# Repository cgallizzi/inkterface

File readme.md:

# Inkterface: Now Playing Edition

An e-ink faceplate for your Steam Machine that shows the box art, playtime,
and achievement progress of whatever you're playing — plus all the original
system telemetry readouts.

> This is a community fork of
> [Valve's Inkterface](https://gitlab.steamos.cloud/SteamHardware/SteamMachine/inkterface),
> created by NaKyle Wright at Valve and released under the MIT license.
> All of the hardware design, assembly docs, and the original firmware and
> companion app are their work — this fork adds the artwork/"now playing"
> features and easier install tooling on top. Thank you Valve for open
> sourcing it!

## What this fork adds

* **Now Playing artwork mode**: when you launch a game, the panel switches to
  that game's box art with your total playtime and achievement progress
  rendered next to it (dithered for the e-ink look). When you quit, it goes
  back to the regular telemetry layout. Toggle it with the `Box Art` button
  in the configure screen.
* **Game collectors**: `Game Time` and `Achievements` readouts you can put in
  any panel field, alongside the stock CPU/GPU/fan stats.
* **Browser firmware flasher**: flash your Feather from Chrome/Edge at the
  project's GitHub Pages site — no toolchain install needed.
* **One-line app install**: paste a single command on your Steam Machine and
  you're done — no building, no USB sticks.

Achievement data comes from the Steam Community profile endpoint and requires
no API key, but your profile's game details need to be public for it to show.

## Quick Install (this fork)

**Firmware** — plug the Feather into any PC over USB and open the
[web flasher](https://cgallizzi.github.io/inkterface/) in Chrome or Edge, then
click Install for your board.

**App** — on the Steam Machine, open a terminal in desktop mode and run:

```sh
curl -fsSL https://raw.githubusercontent.com/cgallizzi/inkterface/main/scripts/install.sh | sh
```

That downloads the latest release to `~/Applications`, launches it, and from
there you pick your panel and click Install (bottom right) to set up the
background service. Prebuilt AppImages are also on the
[releases page](https://github.com/cgallizzi/inkterface/releases) if you'd rather
grab one manually.

Everything below is the original upstream documentation for building the
hardware and working from source.

## Required Hardware

* 1 x Adafruit ESP32-S3 Feather w/ 2MB PSRAM
    * [Link to V1 Board, as shown in the assembly video and document!](https://www.adafruit.com/product/5477)
    * [Link to V2 Board, accidentally the only link previously!](https://www.adafruit.com/product/5400)
    * Both the V1 and V2 modules work, but they have different pinouts, make sure
      to check if you see the "V2" silkscreen on your board and choose the correct
      pinout sheet and environment when building the firmware!
* 1 x [Adafruit eInk Breakout Friend](https://www.adafruit.com/product/4224)
* 1 x [Adafruit 5.83" Monochrome eInk Panel](https://www.adafruit.com/product/6397)
* 1 x [LP803860 Battery](https://www.adafruit.com/product/2011)
* 13 x M2.5 x 5mm Pan Head Machine Screws
    * [McMaster](https://www.mcmaster.com/92000A103/)
    * [Amazon](https://www.amazon.com/dp/B0GC58C2V5)
* 4 x [1/4" x 1/4" x 3/16" Stepped Magnet SB443-OUT](https://www.kjmagnetics.com/sb443-out-neodymium-stepped-block-magnet)

## Assembly

Check out the assembly tutorial video in
[the upstream repo](https://gitlab.steamos.cloud/SteamHardware/SteamMachine/inkterface/-/blob/main/docs/Inkterface%20Assembly.mp4)
(kept out of this fork because it exceeds GitHub's file size limit),
or if you'd prefer there is a PDF version too `./docs/Inkterface Assembly.pdf`.

**_Warning: The screws will thread themselves into the plastic, but be VERY gentle
as it is easy to strip the plastic away and you may need to re-print parts!_**

1. Print parts from `./cad` folder.
    * Individual parts are included as separate STEP files, but a combined file
      with all parts that is ready for printing on a Stratasys F370 build plate
      is also provided as `Inkterface - Print Plate.step`.
2. Attach the ESP32 Feather and eInk Breakout to the board plate layer using 4x screws.
    * Having them held in place helps with soldering the connections and sizing your wires.
3. Solder wires between the pins of the two boards.
    * MOSI/MISO/SCK/GND all connect directly as expected.
    * 3V3 from the feather connects to VIN on the breakout.
        * The 3V3 pin on the breakout is a 3V3 output.
    * For the **_V1_** feather connect these pins, like Feather -> Breakout:
        * PIN 6 -> ENA
        * PIN 9 -> BUSY
        * PIN 10 -> RST
        * PIN 11 -> SRCS
        * PIN 12 -> D/C
        * PIN 13 -> ECS
    * For the **_V2_** feather connect these pins, like Feather -> Breakout:
        * PIN 32 -> ENA
        * PIN 15 -> BUSY
        * PIN 33 -> RST
        * PIN 27 -> SRCS
        * PIN 12 -> D/C
        * PIN 13 -> ECS
    * **_NOTE:_** On both feather versions we connect to pins in the same physical
        positions, but they are different logical pins in the firmware.
4. Place the e-ink panel into the matching recess in the faceplate part.
5. Fit the two midplates in.
6. Place the 4 magnets into the recesses in each corner of of the midplates.
    * Magnetic field orientation doesn't matter, they connect to metal slugs
      in the Steam Machine chassis.
7. Place the board plate over the midplates, aligning the magnets and screw holes.
8. Fasten the boardplate with 8x screws in the screw holes along the edges.
9. Connect the e-ink panel to the breakout board.
    * Be careful when handling the flex that comes out of the panel, it is fragile
      and should not be bent or folded.
10. Place the battery in the recess, tucking its wire under the board plate and
    up into the clearance hole beside the feather.
11. Insert and fasten down the battery retainer/cover.
12. Plug the battery connecor into the feather.

Once you've assembled the unit it should be fairly solid and easily magnet to the
front of a Steam Machine!

You will need to build/flash the firmware onto the feather using the steps below.

## Usage

[Eventually we'll have an app up on Steam](https://store.steampowered.com/app/1222770)
but until then you can build an AppImage using the instructions further down in
this readme.

Once you have it built, take a look at `./docs/Inkterface Setup.pdf`, but the
basics are:
1. Enable bluetooth.
2. In desktop mode register as an app in Steam.
    * Or you can just run it directly.
3. Wait for it to discover your panel.
    * If it doesn't appear try clicking the reset button on the back and checking
      that bluetooth is enabled.
4. Select your panel, the name shown should match what's displayed on the inkterface.
    * They all start with an `INKTF-` prefix and then use a unique portion of the
      panels BLE MAC address.
5. On the configure screen, install the service using the button at the bottom
   right.
    * This will set itself up as a user service, so don't move the AppImage or
      that will break, no biggie though, you'll just need to re-run it.
    * Once the service is installed it might take 10-20 seconds for it to connect
      to the inkterface, that's fine, it just needs to go through discovery.
6. Finally you can click any of the readouts to adjust what they display.
    * We have several stats built in, but if you check out `include/panel-state.hpp`
      you can add any function that can return a `QString` or `double` and then
      `registerCollector()` to have it show up in the list.
      * There are some examples of stateful and idempotent collectors in `SysStats`,
        they get registered in the `PanelState` constructor.
7. Exit the configuration app.
    * The service is lightweight and runs in the background, you only need to
      run the config software to select a panel or to change what it displays.

## Building Interface

If you have Qt installed you should be able to open the cmake project in Qt Creator
and use that.

For better distributable builds you can setup a container for wider platform
support using the included `Containerfile`.

1. `podman build -t qt69-builder -f ./Containerfile`
2. `distrobox create --image qt69-builder --name qt69`
3. `distrobox enter qt69`
4. `./scripts/build.sh deploy`

That should produce an AppImage for you in the `./dist-linux-x86_64` folder.

This container uses an older version of Ubuntu and Qt 6.9 which should let us
build AppImages that will work on a wide range of modern systems.

## Building Firmware

For a mix of convenience and approachability this project uses
[PlatformIO](https://platformio.org), and in particular here you'll use the
[pio run](https://docs.platformio.org/en/latest/core/userguide/cmd_run.html)
command. Reading up on them can be useful, especial options like `--upload-port`
which could help if you have multiple serial ports.

If you're using the container from above you can just do:

1. `distrobox enter qt69`
2. `cd ./firmware`
3. If you have a **_V1_** feather: `pio run -e featherv1 -t upload`
4. If you have a **_V2_** feather: `pio run -e featherv2 -t upload`

And it should build and flash the firmware, if you want to get setup manually:

1. Install [PlatformIO](https://platformio.org) for your system.
2. `cd ./firmware`
3. If you have a **_V1_** feather: `pio run -e featherv1 -t upload`
4. If you have a **_V2_** feather: `pio run -e featherv2 -t upload`

Of course in both cases you need to have the ESP32 Feather attached via USB and
permission to interact with serial devices on your system.

**_NOTE:_** You can add build definitions and support for other boards by modifying
the `platformio.ini`, check it out to see the V1 and V2 feather environments.

## Design Docs

Planning out the UI and panel design is done in a Lunacy document you can find
in the `./design` folder.

Lunacy is an open source alternative to tools like Figma that can work entirely
offline.

## License

This project is licensed under the MIT License, see LICENSE.

This project depends on third-party software that is distributed under its own
licenses. Those licenses remain applicable to the respective components and
are not modified by this project's license.

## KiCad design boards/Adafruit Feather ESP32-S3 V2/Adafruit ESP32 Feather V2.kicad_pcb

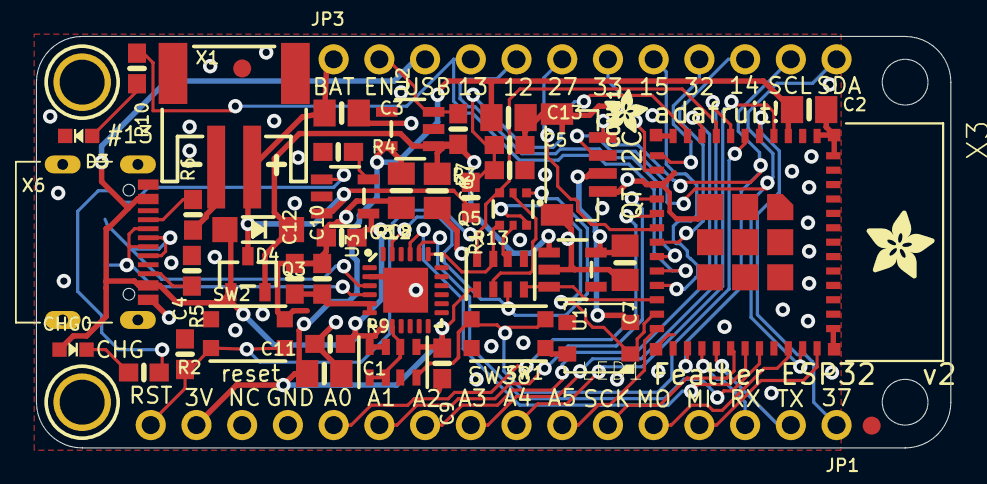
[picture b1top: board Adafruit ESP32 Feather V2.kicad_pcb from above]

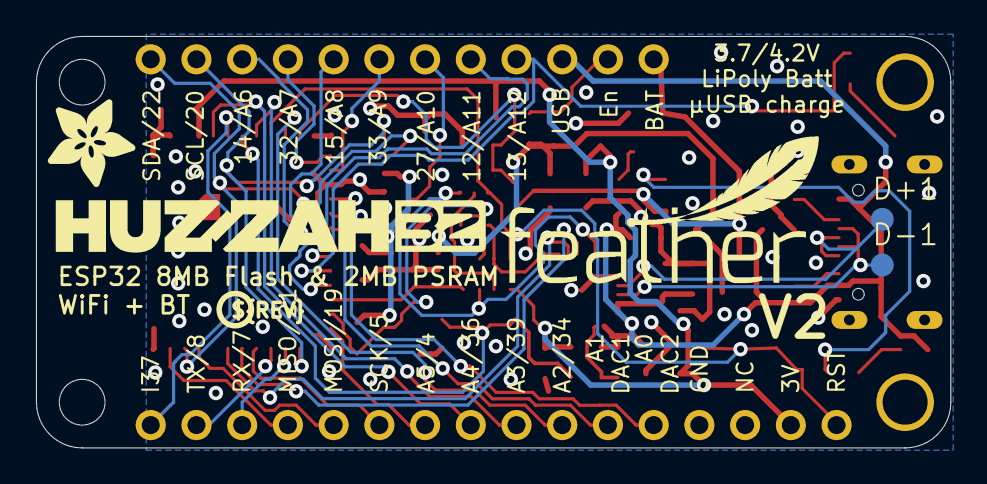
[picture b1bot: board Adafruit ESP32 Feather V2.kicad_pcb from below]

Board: 2 copper layers, 50.8 x 22.9 mm, 56 parts (6 on the bottom side), 49 nets.

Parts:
C1, C2, C13: 10uF; 0805-NO
C3, C6, C7, C8: 10µF; 0805-NO
C4, C5, C9, C10: 1uF; 0603-NO
C11, C12: 0.1uF; 0603-NO
CHG0: ORANGE; CHIPLED_0603_NOOUTLINE
CONN1: STEMMA_I2C_QTRA; JST_SH4_RA
D3: RED; CHIPLED_0603_NOOUTLINE
D4: MBR540; SOD-123
D+1: TPB1,27; B1,27_385
D-1: TPB1,27; B1,27_385
IC3: CP2102N-24; QFN24_4MM_SMSC
JP1: 1X16_ROUND
JP3: 1X12_ROUND
LED1: WS2812B3535; LED3535
Q3: DMG3415U; SOT23-R
Q5: DUAL NPN; SOT363
R1, R3: 200K; 0603-NO
R2, R4, R5, R6, R10: 5.1K; 0603-NO
R7, R12: 100K; 0603-NO
R9: 47K; RESPACK_4X0603
R13: 10K; RESPACK_4X0603
SW1, SW2: KMR2; BTN_KMR2_4.6X2.8
U1, U2: AP2112-3.3; SOT23-5
U3: MCP73831T-2ACI/OT; SOT23-5
U$7: ADAFRUIT_5MM
U$9: FEATHERLOGO_MED
U$13: PCBFEAT-REV-040
U$14: ADAFRUIT_2.5MM
U$15: ADAFRUIT_3.5MM
U$31, U$32: MOUNTINGHOLE2.5; MOUNTINGHOLE_2.5_PLATED
U$34, U$35: FIDUCIAL_1MM
U$43: HUZZAH32
UNK_HOLE_0: dummyfp0
UNK_HOLE_1: dummyfp1
X1: JSTPH; JSTPH2_BATT
X3: ESP32-PICO-MINI-02MINI; ESP32-PICO-MINI
X6: USB Type C; USB_C_CUSB31-CFM2AX-01-X

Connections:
3.3V: C1.1, C2.1, C8.1, C9.1, C13.1, JP1.15, R9.5, R13.1, U2.5, X3.3
3.45V: C10.1, C12.1, IC3.5, IC3.6
A0_DAC2: JP1.12, X3.16
A1_DAC1: JP1.11, X3.15
A2_I34: JP1.10, X3.9
A3_I39: JP1.9, X3.7
A4_I36: JP1.8, X3.4
A5_IO4: JP1.7, X3.24
A13_I35: C5.1, R1.1, R3.2, X3.10
CC1: R6.2, X6.A5
CC2: R5.2, X6.B5
D+: D+1.TP, IC3.3, X6.A6, X6.B6
D-: D-1.TP, IC3.4, X6.A7, X6.B7
DTR: IC3.23, Q5.1, R13.3
EN: JP3.2, R7.1, U2.3
GND: C1.2, C2.2, C3.2, C4.2, C5.2, C6.2, C7.2, C8.2, C9.2, C10.2, C11.2, C12.2, C13.2, CONN1.1, CONN1.MT1, CONN1.MT2, D3.C, IC3.2, IC3.THERM, JP1.13, LED1.4, R3.1, R4.1, R5.1, R6.1, R9.3, R12.1, R13.5, SW1.A, SW1.A', SW2.A, SW2.A', U1.2, U2.2, U3.2, X1.1, X1.NC1, X1.NC2, X3.1, X3.2, X3.11, X3.14, X3.36, X3.37, X3.38, X3.39, X3.40, X3.41, X3.42, X3.43, X3.44, X3.45, X3.46, X3.47, X3.48, X3.49, X3.50, X3.51, X3.52, X3.53, X3.54, X3.55, X3.56, X3.57, X3.58, X3.59, X3.60, X3.61, X6.A1B12, X6.B1A12
GPIO0: LED1.1, Q5.6, X3.23
I37: JP1.1, X3.5
IO12_A11: JP3.5, X3.19
IO13_A12: JP3.4, R10.1, X3.20
IO14_A6: JP3.10, X3.18
IO15_A8: JP3.8, X3.21
IO27_A10: JP3.6, X3.17
IO32_A7: JP3.9, X3.12
IO33_A9: JP3.7, X3.13
MISO: JP1.4, X3.35
MOSI: JP1.5, X3.33
unnamed: CHG0.C, R2.1
unnamed: R2.2, U3.1
unnamed: R4.2, U3.5
unnamed: D3.A, R10.2
unnamed: R9.4, SW1.B, SW1.B', X3.6
unnamed: Q5.5, R13.6
unnamed: Q5.2, R13.2
NEOI2C_PWR: R13.4, U1.3, X3.22
RTS: IC3.19, Q5.4, R13.7
RX/IO7: JP1.3, X3.27
RXD0: IC3.21, X3.30
SCK: JP1.6, X3.29
SCL: CONN1.4, JP3.11, X3.26
SDA: CONN1.3, JP3.12, X3.34
TX/IO8: JP1.2, X3.28
TXD0: IC3.20, X3.31
VBAT: C3.1, JP3.1, Q3.3, R1.2, U3.3, X1.2
VBUS: C11.1, CHG0.A, D4.A, IC3.7, JP3.3, Q3.1, R9.7, R9.8, R12.2, U3.4, X6.A4B9, X6.B4A9
VBUS_DET: IC3.8, R9.1, R9.2, R9.6
VHI: C6.1, D4.C, Q3.2, R7.2, U1.1, U2.1
V_NEOI2C: C7.1, CONN1.2, LED1.2, U1.5
~RESET: C4.1, JP1.16, Q5.3, R13.8, SW2.B, SW2.B', X3.8

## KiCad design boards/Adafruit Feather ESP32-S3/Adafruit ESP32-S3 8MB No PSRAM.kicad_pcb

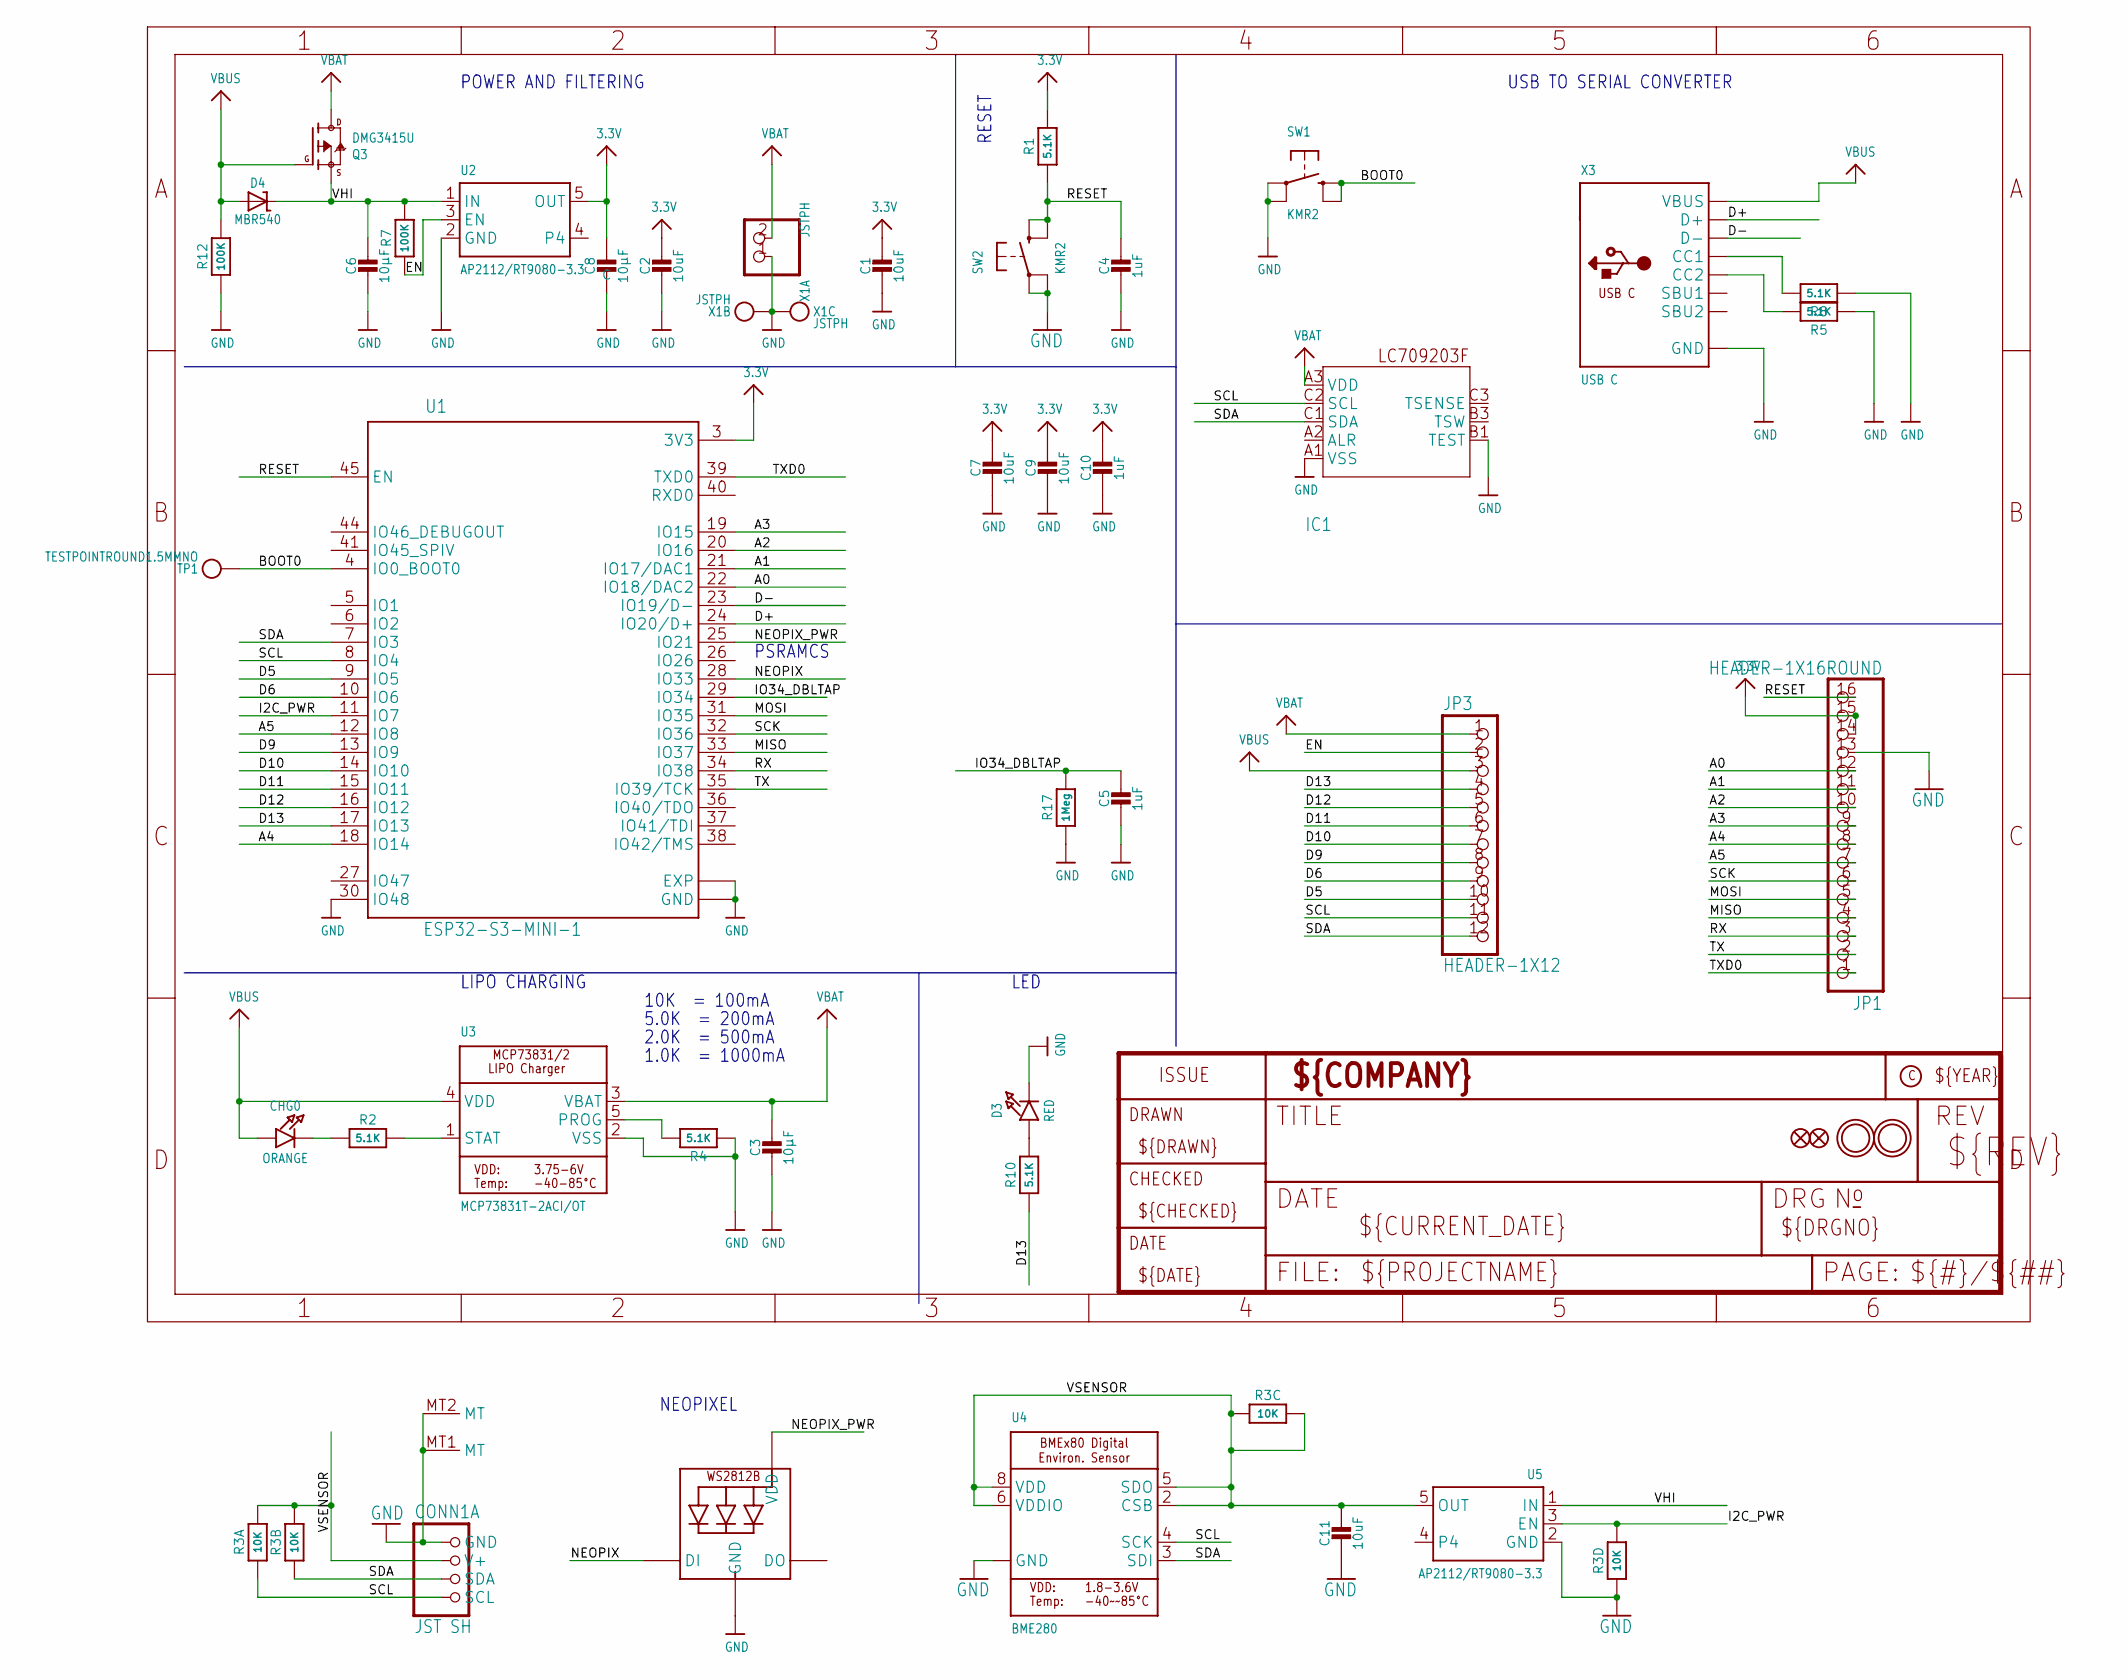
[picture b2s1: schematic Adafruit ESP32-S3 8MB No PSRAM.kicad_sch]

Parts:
C1, C2, C7, C9: 10uF; 0805-NO
C3, C6, C8: 10µF; 0805-NO
C4, C5, C10: 1uF; 0603-NO
C11: 10uF; _0805MP
CHG0: ORANGE; CHIPLED_0603_NOOUTLINE
CONN1: JST SH; JST_SH4_RA
D3: RED; CHIPLED_0603_NOOUTLINE
D4: MBR540; SOD-123
IC1: LC709203F/MH; WLCSP9
JP1: HEADER-1X16ROUND; 1X16_ROUND
JP3: HEADER-1X12; 1X12_ROUND
LED1: WS2812B_SK6805_1515; SK6805_1515
Q3: DMG3415U; SOT23-R
R1, R2, R4, R5, R8, R10: 5.1K; 0603-NO
R3: 10K; RESPACK_4X0603
R7, R12: 100K; 0603-NO
R17: 1Meg; 0603-NO
SW1, SW2: KMR2; BTN_KMR2_4.6X2.8
TP1: TESTPOINTROUND1.5MMNO; TESTPOINT_ROUND_1.5MM_NO
U1: ESP32-S3-MINI-1; QFN60_ESP32-S2-MINI-1_EXP
U2, U5: AP2112/RT9080-3.3; SOT23-5
U3: MCP73831T-2ACI/OT; SOT23-5
U4: BME280
U$31, U$32: MOUNTINGHOLE2.5; MOUNTINGHOLE_2.5_PLATED
U$34, U$35: FIDUCIAL_1MM
X1: JSTPH; JSTPH2_BATT
X3: USB C; USB_C_CUSB31-CFM2AX-01-X

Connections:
3.3V: C1.1, C2.1, C7.1, C8.1, C9.1, C10.1, JP1.14, JP1.15, R1.2, U1.3 (3V3), U2.5 (OUT)
A0: JP1.12, U1.22 (IO18/DAC2)
A1: JP1.11, U1.21 (IO17/DAC1)
A2: JP1.10, U1.20 (IO16)
A3: JP1.9, U1.19 (IO15)
A4: JP1.8, U1.18 (IO14)
A5: JP1.7, U1.12 (IO8)
BOOT0: SW1.B (S), SW1.B' (S1), TP1.P$1, U1.4 (IO0_BOOT0)
D5: JP3.10, U1.9 (IO5)
D6: JP3.9, U1.10 (IO6)
D9: JP3.8, U1.13 (IO9)
D10: JP3.7, U1.14 (IO10)
D11: JP3.6, U1.15 (IO11)
D12: JP3.5, U1.16 (IO12)
D13: JP3.4, R10.1, U1.17 (IO13)
D+: U1.24 (IO20/D+), X3.A6 (D+), X3.B6 (D+)
D-: U1.23 (IO19/D-), X3.A7 (D-), X3.B7 (D-)
EN: JP3.2, R7.1, U2.3 (EN)
GND: C1.2, C2.2, C3.2, C4.2, C5.2, C6.2, C7.2, C8.2, C9.2, C10.2, C11.2, CONN1.1 (GND), CONN1.MT1 (MT), CONN1.MT2 (MT), D3.C, IC1.A1 (VSS), IC1.B1 (TEST), JP1.13, LED1.4 (GND), R3.4 (1), R4.1, R5.1, R8.1, R12.1, R17.1, SW1.A, SW1.A' (P1), SW2.A, SW2.A' (P1), U1.1 (GND), U1.2 (GND), U1.30 (IO48), U1.42 (GND), U1.43 (GND), U1.46 (GND), U1.47 (GND), U1.48 (GND), U1.49 (GND), U1.50 (GND), U1.51 (GND), U1.52 (GND), U1.53 (GND), U1.54 (GND), U1.55 (GND), U1.56 (GND), U1.57 (GND), U1.58 (GND), U1.59 (GND), U1.60 (GND), U1.61 (EXP), U1.62 (GND), U1.63 (GND), U1.64 (GND), U1.65 (GND), U1.66 (EXP), U1.67 (EXP), U1.68 (EXP), U1.69 (EXP), U1.70 (EXP), U1.71 (EXP), U1.72 (EXP), U1.73 (EXP), U2.2 (GND), U3.2 (VSS), U4.1 (GND), U4.7 (GND), U5.2 (GND), X1.1, X1.NC1, X1.NC2, X3.A1B12 (GND), X3.B1A12 (GND)
I2C_PWR: R3.5 (2), U1.11 (IO7), U5.3 (EN)
IO34_DBLTAP: C5.1, R17.2, U1.29 (IO34)
MISO: JP1.4, U1.33 (IO37)
MOSI: JP1.5, U1.31 (IO35)
unnamed: CHG0.C, R2.1
unnamed: R2.2, U3.1 (STAT)
unnamed: R4.2, U3.5 (PROG)
unnamed: D3.A, R10.2
unnamed: R8.2, X3.A5 (CC1)
unnamed: R5.2, X3.B5 (CC2)
NEOPIX: LED1.1 (DI), U1.28 (IO33)
NEOPIX_PWR: LED1.2 (VDD), U1.25 (IO21)
RESET: C4.1, JP1.16, R1.1, SW2.B (S), SW2.B' (S1), U1.45 (EN)
RX: JP1.3, U1.34 (IO38)
SCK: JP1.6, U1.32 (IO36)
SCL: CONN1.4 (SCL), IC1.C2 (SCL), JP3.11, R3.1, U1.8 (IO4), U4.4 (SCK)
SDA: CONN1.3 (SDA), IC1.C1 (SDA), JP3.12, R3.2 (1), U1.7 (IO3), U4.3 (SDI)
TX: JP1.2, U1.35 (IO39/TCK)
TXD0: JP1.1, U1.39 (TXD0)
VBAT: C3.1, IC1.A3 (VDD), JP3.1, Q3.3 (D), U3.3 (VBAT), X1.2
VBUS: CHG0.A, D4.A, JP3.3, Q3.1 (G), R12.2, U3.4 (VDD), X3.A4B9 (VBUS), X3.B4A9 (VBUS)
VHI: C6.1, D4.C, Q3.2 (S), R7.2, U2.1 (IN), U5.1 (IN)
VSENSOR: C11.1, CONN1.2 (V+), R3.3 (1), R3.6 (2), R3.7 (2), R3.8 (2), U4.2 (CSB), U4.5 (SDO), U4.6 (VDDIO), U4.8 (VDD), U5.5 (OUT)

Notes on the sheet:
NEOPIXEL
5.0K = 200mA
RESET
1.0K = 1000mA
POWER AND FILTERING
LIPO CHARGING
USB TO SERIAL CONVERTER
2.0K = 500mA
PSRAMCS
10K = 100mA
LED

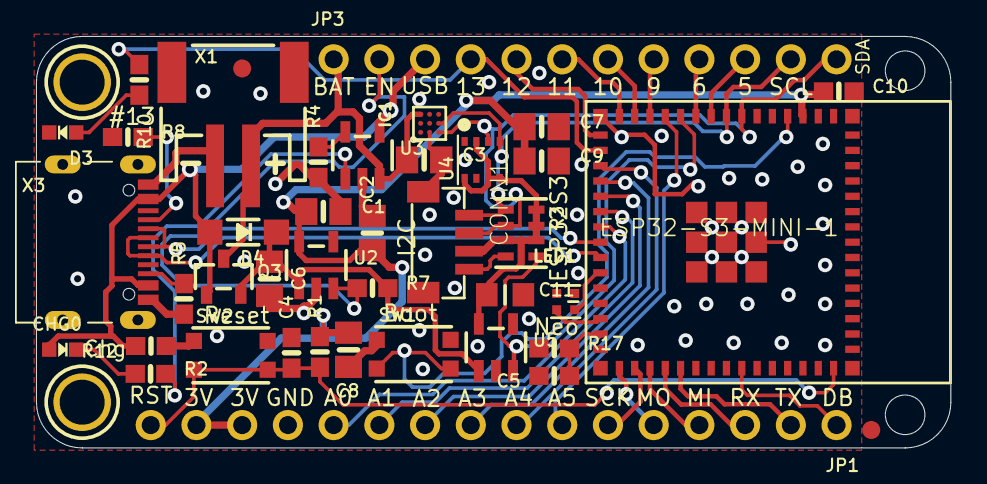
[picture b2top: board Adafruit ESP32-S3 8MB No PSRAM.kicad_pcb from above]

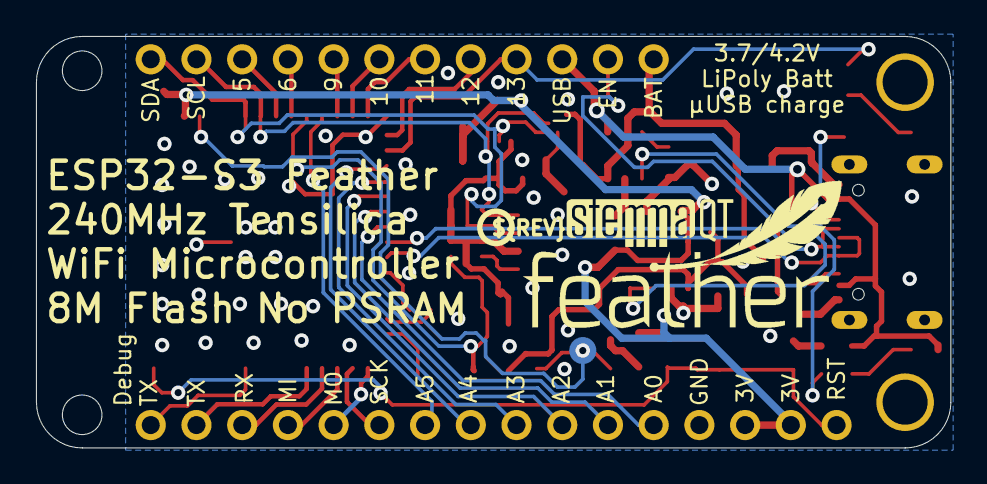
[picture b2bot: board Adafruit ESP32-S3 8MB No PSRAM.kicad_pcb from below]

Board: 2 copper layers, 50.8 x 22.9 mm, 49 parts (4 on the bottom side), 42 nets.

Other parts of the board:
U$14: PCBFEAT-REV-040
U$15: FEATHERLOGO_MED
U$53: STEMMAQT
UNK_HOLE_0: dummyfp0
UNK_HOLE_1: dummyfp1

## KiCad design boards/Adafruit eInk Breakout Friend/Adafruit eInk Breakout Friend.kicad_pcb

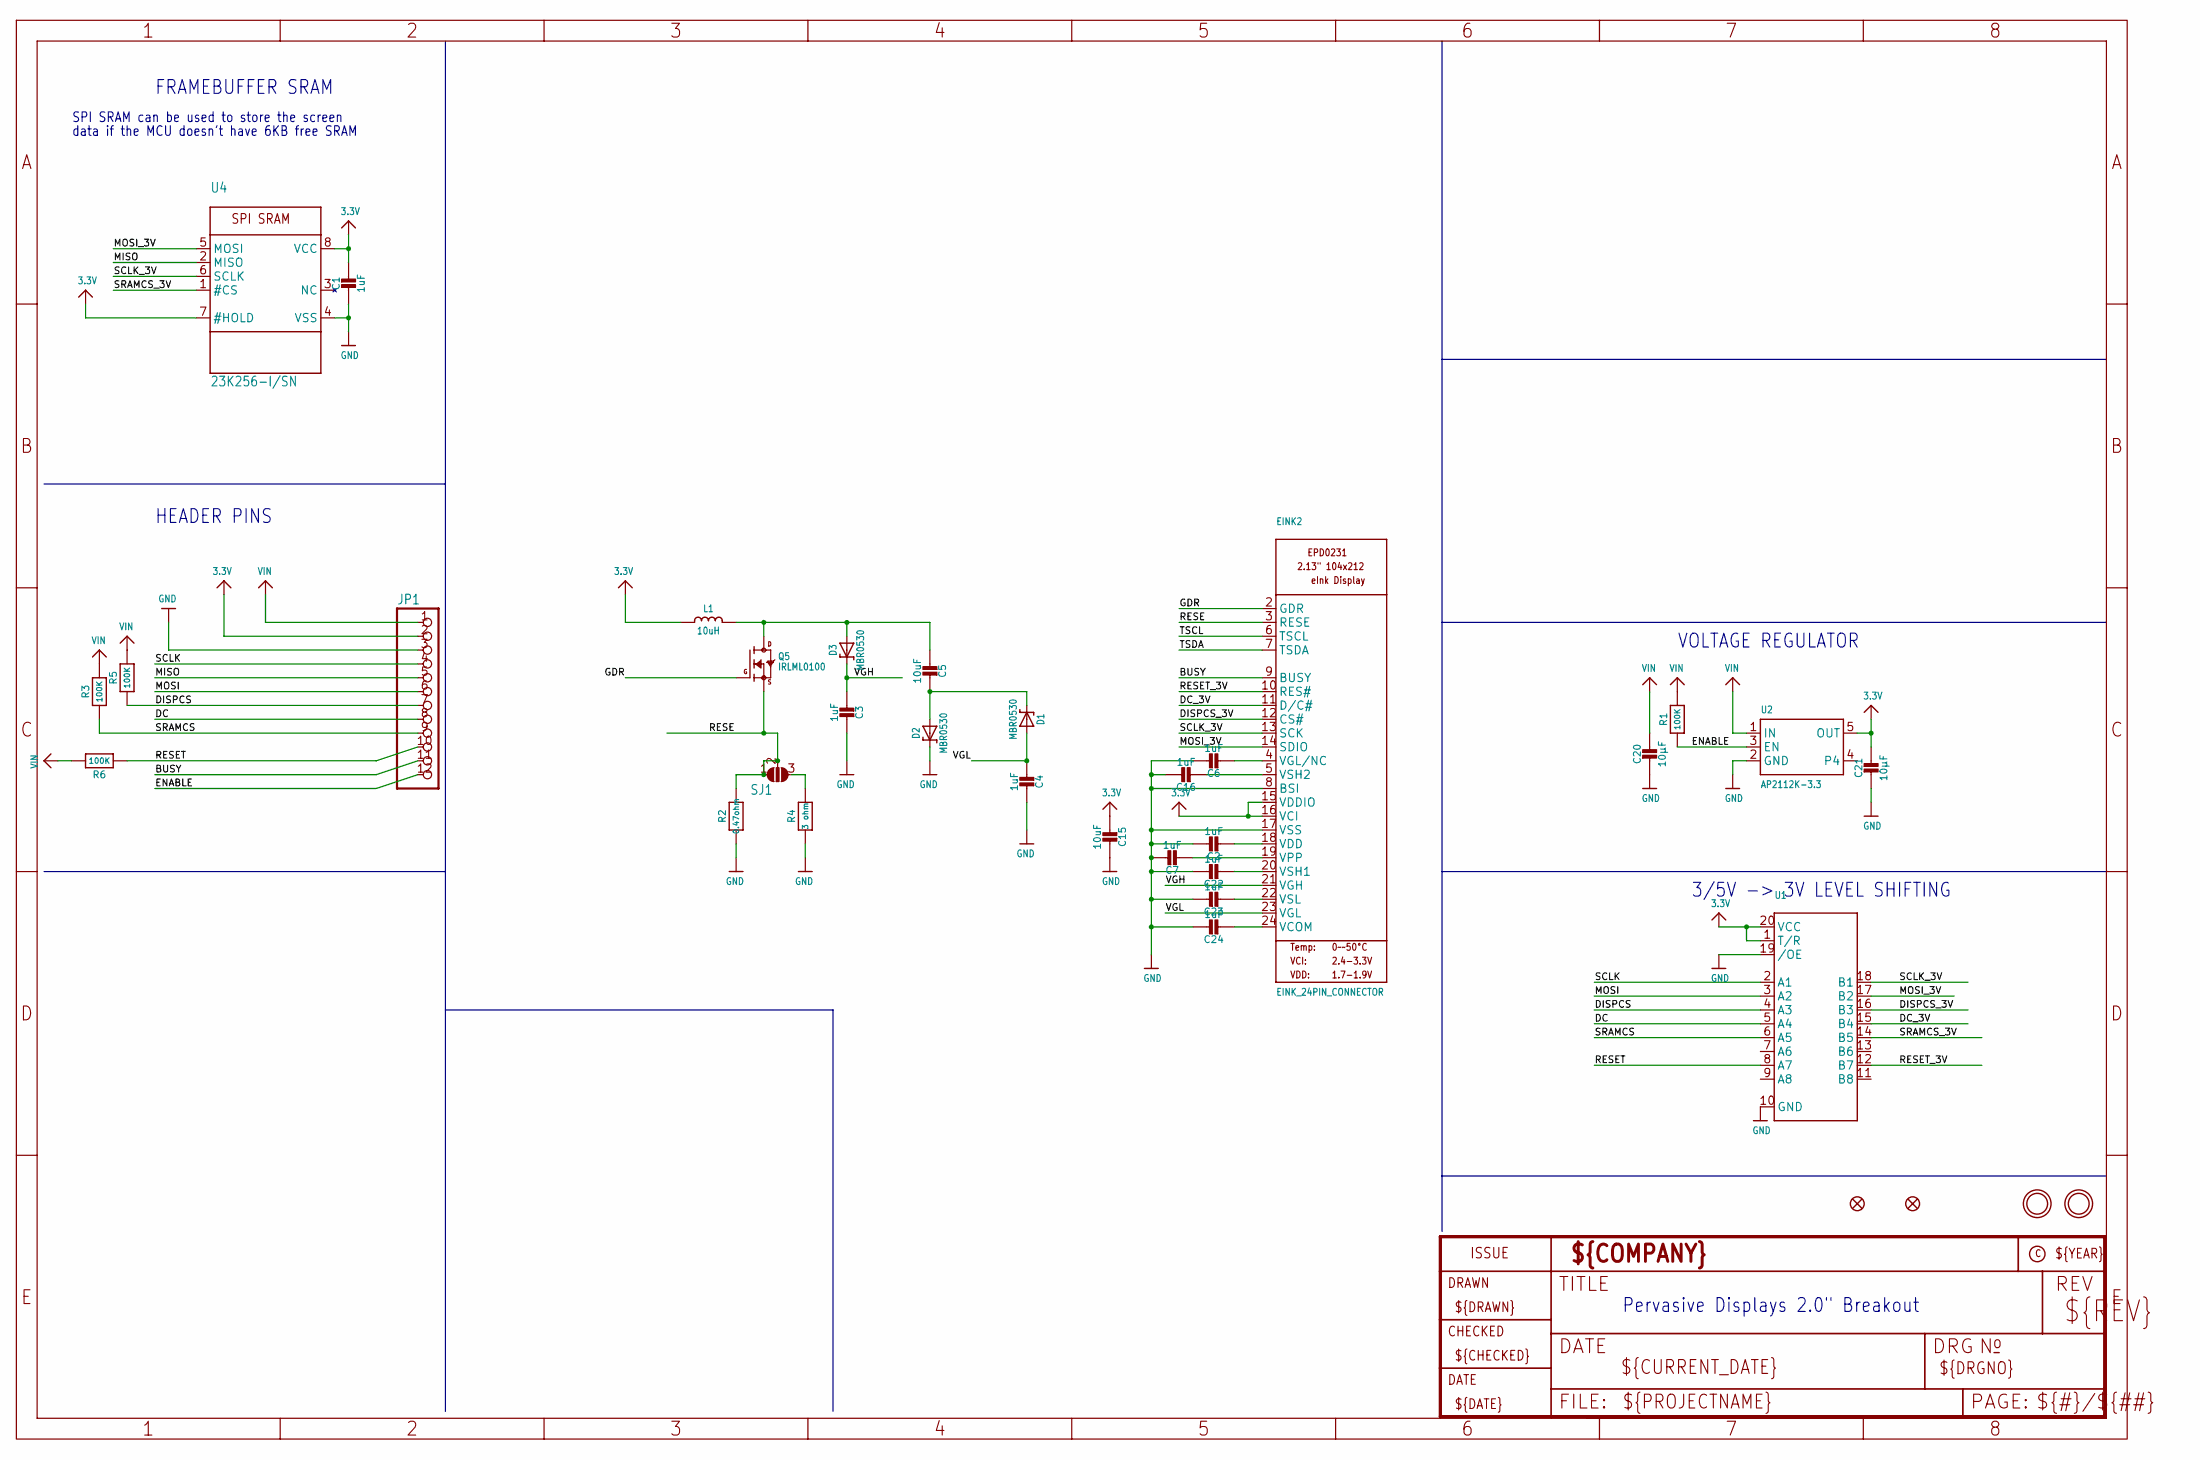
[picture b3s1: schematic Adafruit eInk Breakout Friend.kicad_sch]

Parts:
C1: 1uF; 0805_10MGAP
C2, C3, C4, C6, C7, C16, C22, C23, C24: 1uF; 0805-NO
C5, C15: 10uF; 0805-NO
C20, C21: 10µF; 0805-NO
D1, D2, D3: MBR0530; SOD-123
EINK2: EINK_24PIN_CONNECTOR; EINK_24PIN
FID2, FID3: FIDUCIAL_1MM
JP1: HEADER-1X1276MIL; 1X12_ROUND_76MIL
L1: 10uH; INDUCTOR_4X4MM_NR401
Q5: IRLML0100; SOT23-3
R1, R3, R5, R6: 100K; 0603-NO
R2: 0.47ohm; 0805-NO
R4: 3 ohm; 0805-NO
SJ1: SOLDERJUMPER_2WAY; SOLDERJUMPER_2WAY_OPEN_NOPASTE
U1: 74LCX245; TSSOP20
U2: AP2112K-3.3; SOT23-5
U4: 23K256-I/SN; SOIC8_150MIL
U$3, U$4: MOUNTINGHOLE2.5; MOUNTINGHOLE_2.5_PLATED

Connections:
3.3V: C1.1, C15.2, C21.1, EINK2.15 (VDDIO), EINK2.16 (VCI), JP1.2, L1.P$2 (2), U1.1 (T/R), U1.20 (VCC), U2.5 (OUT), U4.7 (#HOLD), U4.8 (VCC)
BUSY: EINK2.9 (BUSY), JP1.11
DC: JP1.8, U1.5 (A4)
DC_3V: EINK2.11 (D/C#), U1.15 (B4)
DISPCS: JP1.7, R5.1, U1.4 (A3)
DISPCS_3V: EINK2.12 (CS#), U1.16 (B3)
ENABLE: JP1.12, R1.1, U2.3 (EN)
GDR: EINK2.2 (GDR), Q5.1 (G)
GND: C1.2, C2.1, C3.2, C4.2, C6.1, C7.1, C15.1, C16.1, C20.2, C21.2, C22.1, C23.1, C24.1, D2.C, EINK2.8 (BSI), EINK2.17 (VSS), JP1.3, R2.2, R4.2, U1.10 (GND), U1.19 (/OE), U2.2 (GND), U4.4 (VSS)
MISO: JP1.5, U4.2 (MISO)
MOSI: JP1.6, U1.3 (A2)
MOSI_3V: EINK2.14 (SDIO), U1.17 (B2), U4.5 (MOSI)
unnamed: C7.2, EINK2.19 (VPP)
unnamed: C5.2, D1.C, D2.A
unnamed: C5.1, D3.A, L1.P$1 (1), Q5.3 (D)
unnamed: C16.2, EINK2.5 (VSH2)
unnamed: C2.2, EINK2.18 (VDD)
unnamed: C22.2, EINK2.20 (VSH1)
unnamed: R4.1, SJ1.3
unnamed: C6.2, EINK2.4 (VGL/NC)
unnamed: C23.2, EINK2.22 (VSL)
unnamed: C24.2, EINK2.24 (VCOM)
RESE: EINK2.3 (RESE), Q5.2 (S), R2.1, SJ1.1, SJ1.2
RESET: JP1.10, R6.1, U1.8 (A7)
RESET_3V: EINK2.10 (RES#), U1.12 (B7)
SCLK: JP1.4, U1.2 (A1)
SCLK_3V: EINK2.13 (SCK), U1.18 (B1), U4.6 (SCLK)
SRAMCS: JP1.9, R3.1, U1.6 (A5)
SRAMCS_3V: U1.14 (B5), U4.1 (#CS)
TSCL: EINK2.6 (TSCL)
TSDA: EINK2.7 (TSDA)
VGH: C3.1, D3.C, EINK2.21 (VGH)
VGL: C4.1, D1.A, EINK2.23 (VGL)
VIN: C20.1, JP1.1, R1.2, R3.2, R5.2, R6.2, U2.1 (IN)

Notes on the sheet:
3/5V -> 3V LEVEL SHIFTING
SPI SRAM can be used to store the screen
data if the MCU doesn't have 6KB free SRAM
Pervasive Displays 2.0" Breakout
VOLTAGE REGULATOR
FRAMEBUFFER SRAM
HEADER PINS

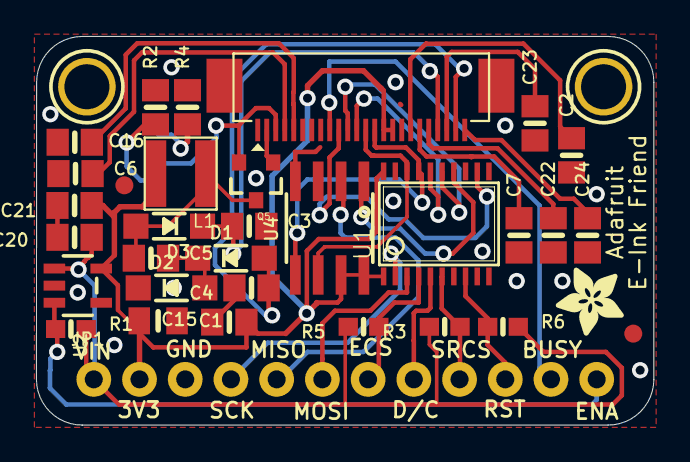
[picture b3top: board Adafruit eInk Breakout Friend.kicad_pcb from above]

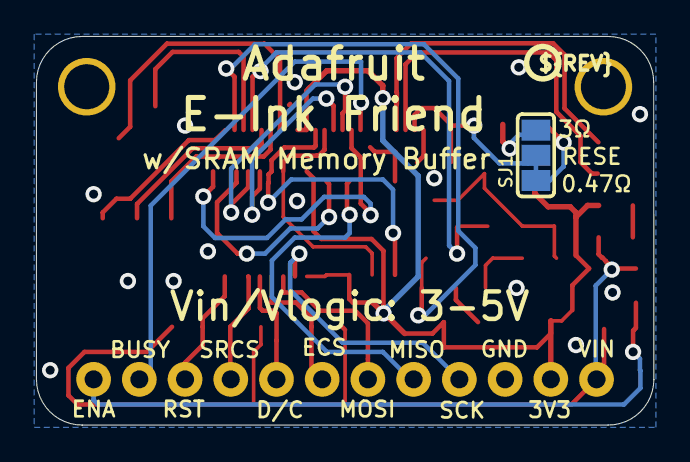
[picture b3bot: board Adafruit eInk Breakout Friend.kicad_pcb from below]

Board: 2 copper layers, 34.3 x 21.6 mm, 37 parts (2 on the bottom side), 32 nets.

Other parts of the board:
U$2: ADAFRUIT_3.5MM
U$9: PCBFEAT-REV-040

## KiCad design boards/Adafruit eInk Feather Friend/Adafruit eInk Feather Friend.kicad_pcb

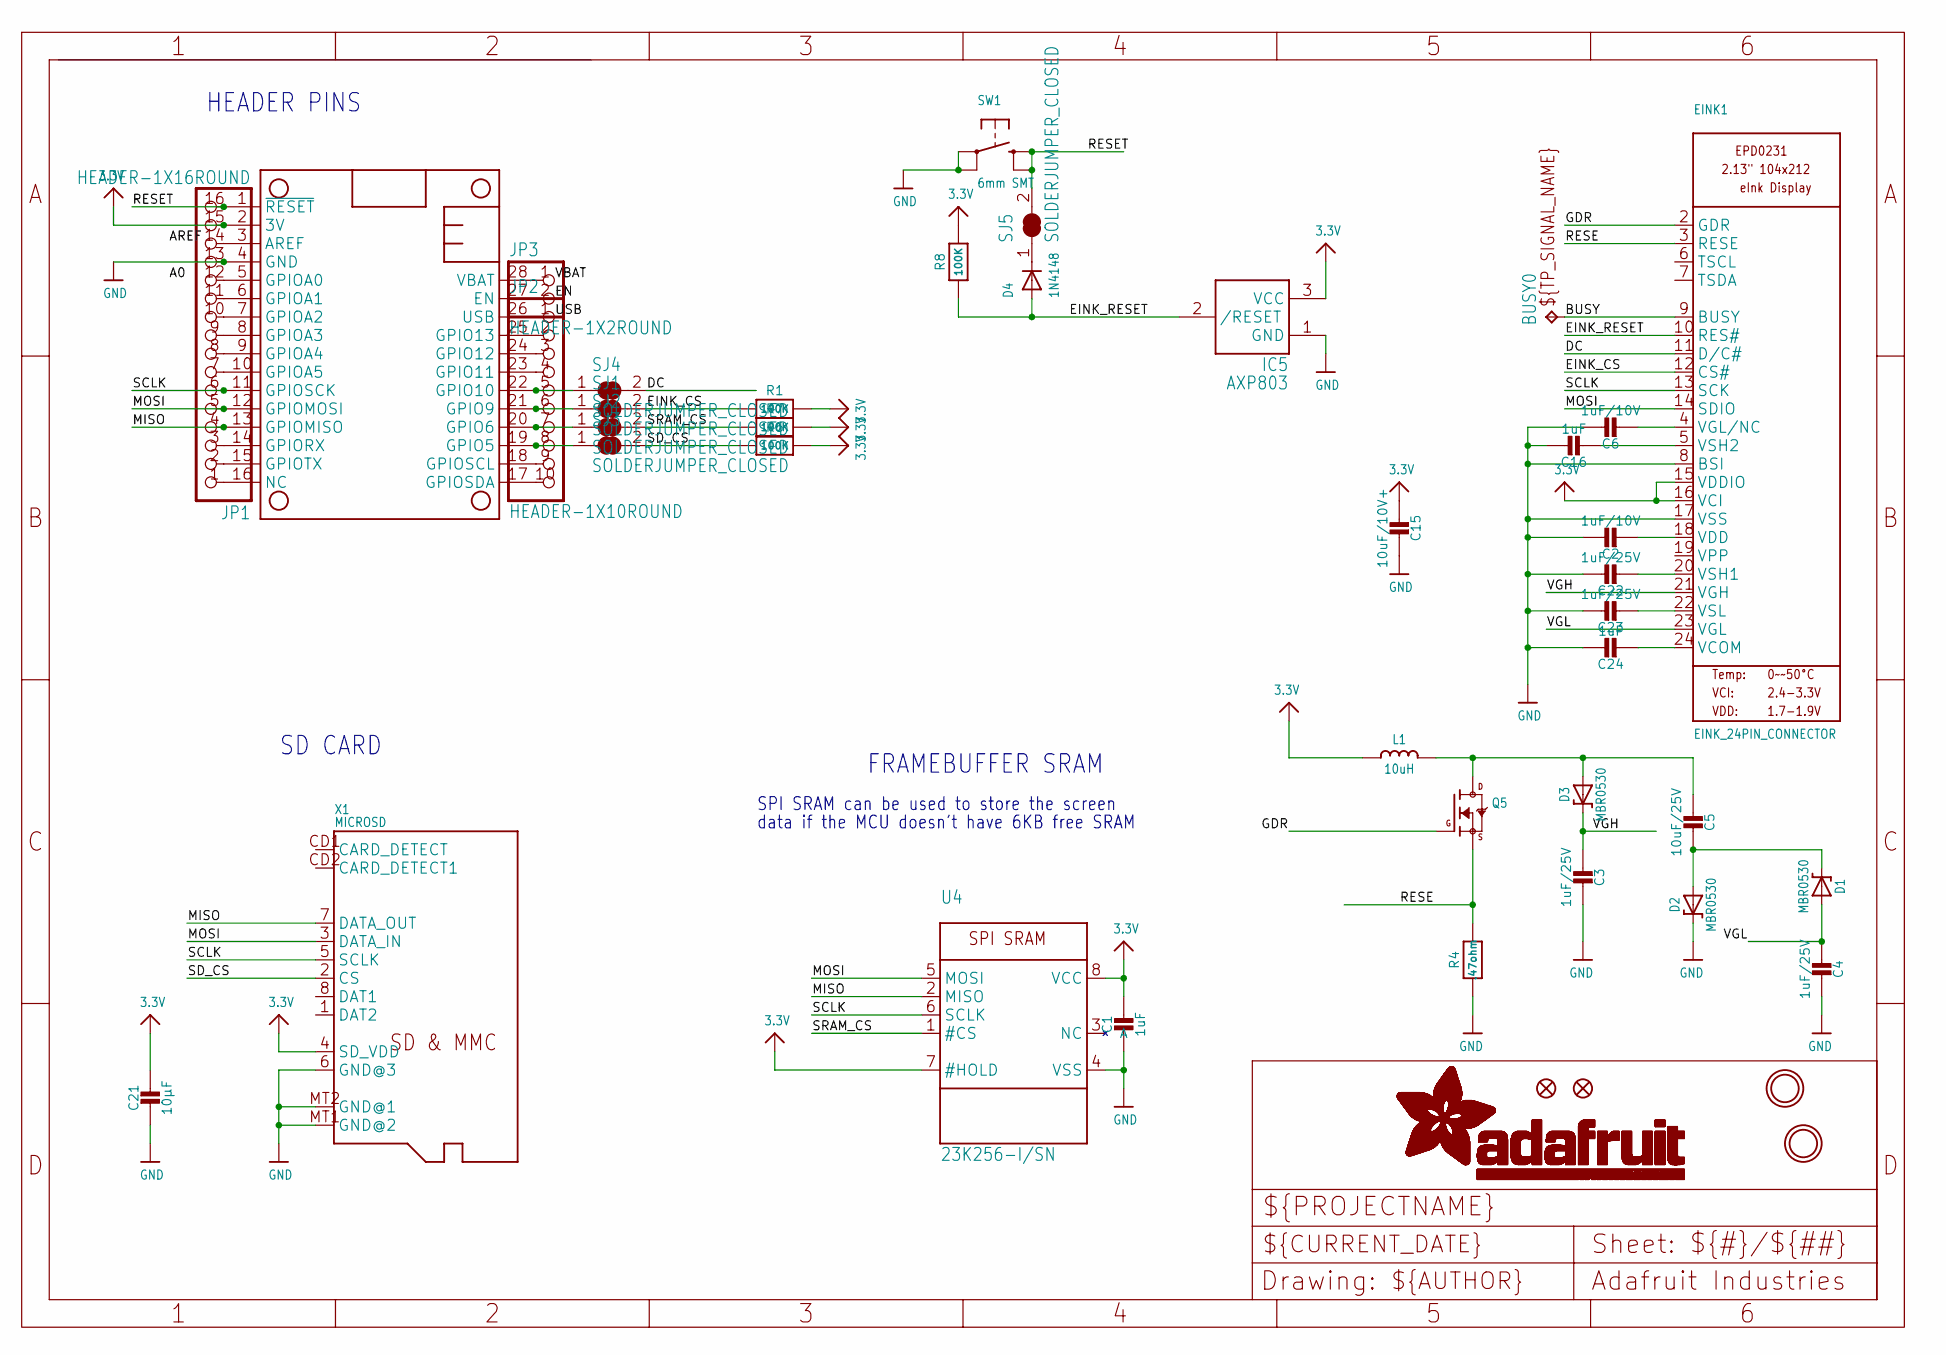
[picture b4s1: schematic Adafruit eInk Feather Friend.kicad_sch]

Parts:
BUSY0: TPTP15SQ; TP15SQ
C1: 1uF; 0805_10MGAP
C2, C6: 1uF/10V; 0805-NO
C3, C4, C22, C23: 1uF/25V; 0805-NO
C5: 10uF/25V; 0805-NO
C15: 10uF/10V+; 0805-NO
C16, C24: 1uF; 0805-NO
C21: 10µF; 0805-NO
D1, D2, D3: MBR0530; SOD-123
D4: 1N4148; SOD-323F
EINK1: EINK_24PIN_CONNECTOR; EINK_24PIN
FID1, FID3: FIDUCIAL_1MM
IC5: AXP803; SOT23
JP1: HEADER-1X16ROUND; 1X16_ROUND
JP2: HEADER-1X10ROUND; 1X10_ROUND
JP3: HEADER-1X2ROUND; 1X02_ROUND
L1: 10uH; INDUCTOR_4X4MM_NR401
MS1: FEATHERWING_NOHOLES
Q5: IRLML0100; SOT23-3
R1, R6, R7, R8: 100K; 0603-NO
R4: .47ohm; 0805_10MGAP
SJ1, SJ2, SJ3, SJ4, SJ5: SOLDERJUMPER_CLOSED; SOLDERJUMPER_CLOSEDWIRE
SW1: 6mm SMT; BTN_KMR2_4.6X2.8
U4: 23K256-I/SN; SOIC8_150MIL
U$3, U$4: MOUNTINGHOLE2.5; MOUNTINGHOLE_2.5_PLATED
X1: MICROSD

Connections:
3.3V: C1.1, C15.2, C21.1, EINK1.15 (VDDIO), EINK1.16 (VCI), IC5.3 (VCC), JP1.15, L1.P$2 (2), MS1.2 (3V), R1.2, R6.2, R7.2, R8.2, U4.7 (#HOLD), U4.8 (VCC), X1.4 (SD_VDD)
A0: JP1.12, MS1.5 (GPIOA0)
AREF: JP1.14, MS1.3 (AREF)
BUSY: BUSY0.TP, EINK1.9 (BUSY)
DC: EINK1.11 (D/C#), SJ4.2
EINK_CS: EINK1.12 (CS#), R1.1, SJ1.2
EINK_RESET: D4.A, EINK1.10 (RES#), IC5.2 (/RESET), R8.1
EN: JP3.2, MS1.27 (EN)
GDR: EINK1.2 (GDR), Q5.1 (G)
GND: C1.2, C2.1, C3.2, C4.2, C6.1, C15.1, C16.1, C21.2, C22.1, C23.1, C24.1, D2.C, EINK1.8 (BSI), EINK1.17 (VSS), IC5.1 (GND), JP1.13, MS1.4 (GND), R4.2, SW1.A, SW1.A' (P1), U4.4 (VSS), X1.6 (GND@3), X1.MT1 (GND@2), X1.MT2 (GND@1)
H: JP2.8, MS1.19 (GPIO5), SJ3.1
I: JP2.7, MS1.20 (GPIO6), SJ2.1
J: JP2.6, MS1.21 (GPIO9), SJ1.1
K: JP2.5, MS1.22 (GPIO10), SJ4.1
MISO: JP1.4, MS1.13 (GPIOMISO), U4.2 (MISO), X1.7 (DATA_OUT)
MOSI: EINK1.14 (SDIO), JP1.5, MS1.12 (GPIOMOSI), U4.5 (MOSI), X1.3 (DATA_IN)
unnamed: JP1.7, MS1.10 (GPIOA5)
unnamed: C5.2, D1.C, D2.A
unnamed: C5.1, D3.A, L1.P$1 (1), Q5.3 (D)
unnamed: C16.2, EINK1.5 (VSH2)
unnamed: C2.2, EINK1.18 (VDD)
unnamed: C22.2, EINK1.20 (VSH1)
unnamed: D4.C, SJ5.1
unnamed: JP1.11, MS1.6 (GPIOA1)
unnamed: C6.2, EINK1.4 (VGL/NC)
unnamed: JP1.10, MS1.7 (GPIOA2)
unnamed: JP1.9, MS1.8 (GPIOA3)
unnamed: JP1.8, MS1.9 (GPIOA4)
unnamed: JP1.3, MS1.14 (GPIORX)
unnamed: JP1.2, MS1.15 (GPIOTX)
unnamed: JP1.1, MS1.16 (NC)
unnamed: JP2.10, MS1.17 (GPIOSDA)
unnamed: JP2.9, MS1.18 (GPIOSCL)
unnamed: JP2.4, MS1.23 (GPIO11)
unnamed: JP2.3, MS1.24 (GPIO12)
unnamed: JP2.2, MS1.25 (GPIO13)
unnamed: C23.2, EINK1.22 (VSL)
unnamed: C24.2, EINK1.24 (VCOM)
RESE: EINK1.3 (RESE), Q5.2 (S), R4.1
RESET: JP1.16, MS1.1 (~RESET), SJ5.2, SW1.B (S), SW1.B' (S1)
SCLK: EINK1.13 (SCK), JP1.6, MS1.11 (GPIOSCK), U4.6 (SCLK), X1.5 (SCLK)
SD_CS: R6.1, SJ3.2, X1.2 (CS)
SRAM_CS: R7.1, SJ2.2, U4.1 (#CS)
USB: JP2.1, MS1.26 (USB)
VBAT: JP3.1, MS1.28 (VBAT)
VGH: C3.1, D3.C, EINK1.21 (VGH)
VGL: C4.1, D1.A, EINK1.23 (VGL)

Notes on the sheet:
FRAMEBUFFER SRAM
SPI SRAM can be used to store the screen
HEADER PINS
data if the MCU doesn't have 6KB free SRAM
SD CARD
